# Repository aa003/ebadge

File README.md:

Electronic Badge:
Features:
Wi-Fi Connected
2.9" E-ink screen
1000mAh rechargeable Li-Po battery
5-Way switch
USB to Serial

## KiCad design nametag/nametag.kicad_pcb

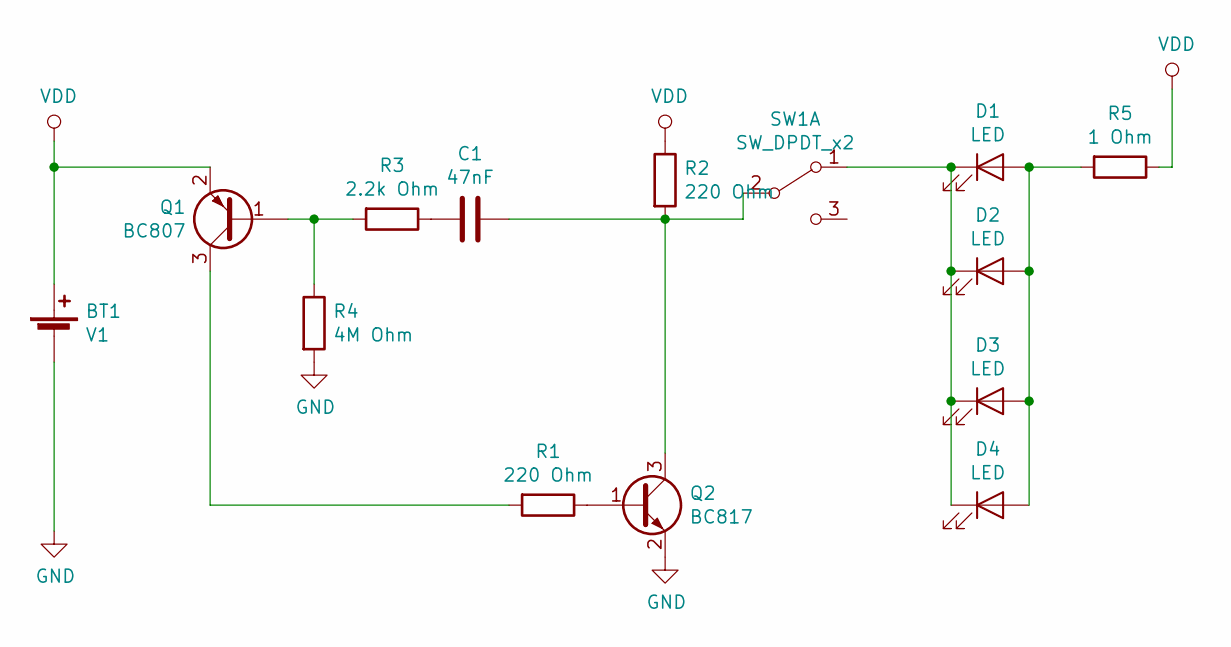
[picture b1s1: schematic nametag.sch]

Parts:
BT1: V1; cr2032_throughhole_holder
C1: 47nF; C_0805_2012Metric
D1, D2, D3, D4: LED; LED_0805_2012Metric
Q1: BC807; SOT-23
Q2: BC817; SOT-23
R1, R2: 220 Ohm; R_0805_2012Metric
R3: 2.2k Ohm; R_0805_2012Metric
R4: 4M Ohm; R_0805_2012Metric
R5: 1 Ohm; R_0805_2012Metric
SW1: SW_DPDT_x2; JS202011CQN

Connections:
GND: BT1.2 (-), Q2.2 (E), R4.2
unnamed: C1.1, Q2.3 (C), R2.2, SW1.2 (B)
unnamed: C1.2, R3.1
unnamed: D1.1 (K), D2.1 (K), D3.1 (K), D4.1 (K), SW1.1 (A)
unnamed: D1.2 (A), D2.2 (A), D3.2 (A), D4.2 (A), R5.2
unnamed: Q1.1 (B), R3.2, R4.1
unnamed: Q1.3 (C), R1.2
unnamed: Q2.1 (B), R1.1
VDD: BT1.1 (+), Q1.2 (E), R2.1, R5.1

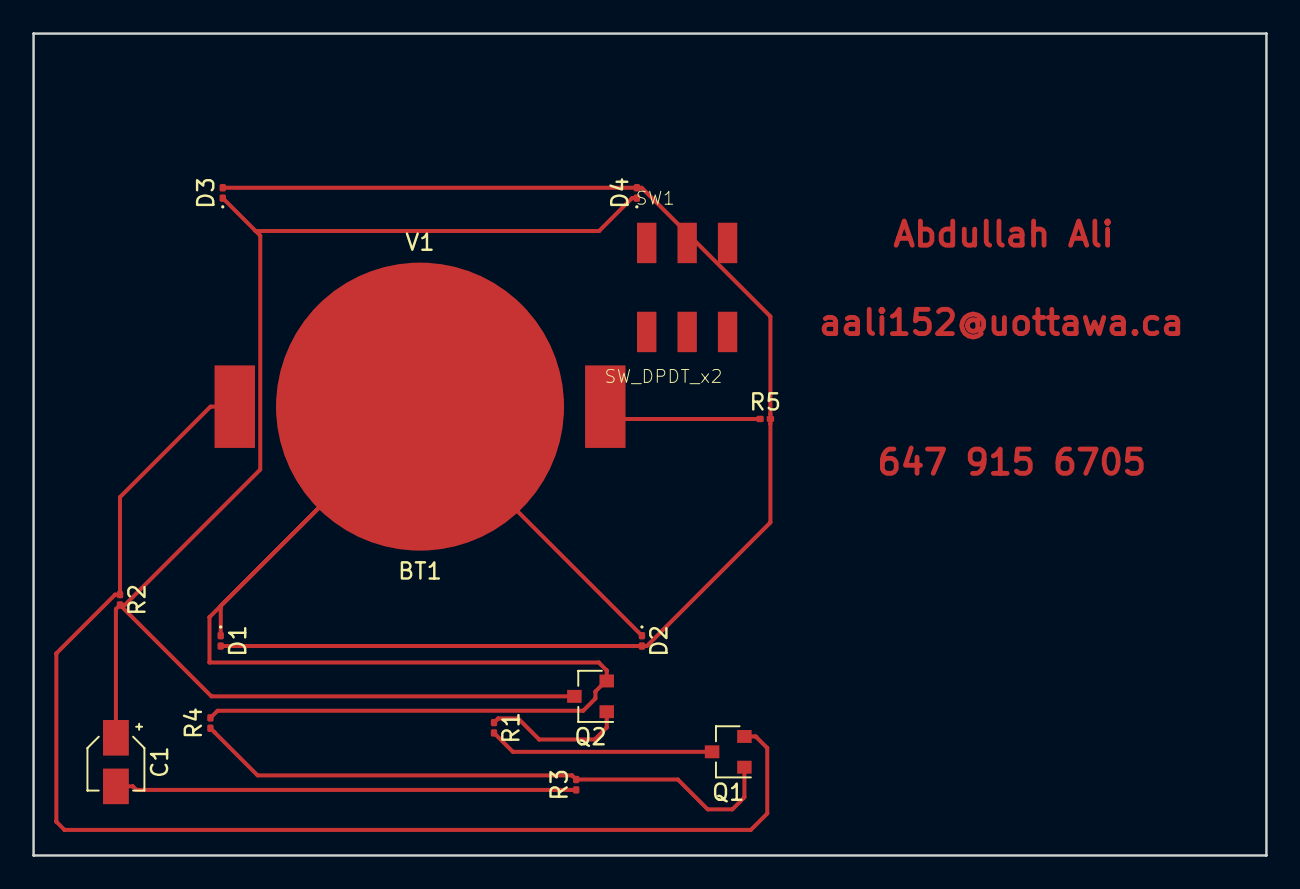
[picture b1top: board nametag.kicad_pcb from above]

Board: 2 copper layers, 76.2 x 50.8 mm, 14 parts (0 on the bottom side), 9 nets.

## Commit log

2019-04-18 added parts list
2019-04-18 added schematics
